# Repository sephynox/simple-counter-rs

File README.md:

# Simple 7-Segment Display Controller

A Rust-based PlatformIO Arduino project for controlling a 4-digit 7-segment
display with incrementing counter functionality. The purpose of this project is
to develop a simple PCB, software, and case design as a template for developing
hardware devices from ideation to production.

## Features

- Efficient multiplexed display using 74HC595 shift registers
- Safe interrupt handling with Mutex
- Hardware abstraction layer for Arduino integration

## Circuit Diagram

## Breadboard Design

## PCB Design

# PCB Assembled

## Case Design

## Hardware Setup

- Arduino Uno R3
- 2x 74HC595 shift registers
- 4-digit 7-segment display (common cathode)
- 2x Ceramic capacitors (100nF)
- 1x 5-pin header for Arduino pins

## Prerequisites

- PlatformIO Core (CLI) or PlatformIO IDE
  ```bash
  cargo install cargo-pio
  ```
- Rust toolchain with AVR target:
  ```bash
  rustup override set nightly
  rustup target add avr-unknown-gnu-atmega328
  ```
- AVR-GCC toolchain
  ```bash
  sudo apt-get install -y gcc-avr binutils-avr avr-libc
  ```

## Install Dependencies

```bash
sudo apt-get install -y python3-venv # If not already installed
cargo install cargo-pio
```

## Building and Flashing

1. Clone the repository:

   ```bash
   git clone https://github.com/sephynox/simple-counter-rs
   cd simple-counter-rs
   ```

2. Build the project:

   ```bash
   cargo pio build
   ```

3. Flash the firmware to your Arduino Uno:

   ```bash
   cargo pio exec -- run --target upload
   ```

## How to Create a New Project

```bash
cargo pio new --board uno your-project-name
```

## License

This project is licensed under the MIT License - see the [LICENSE](LICENSE) file for details.

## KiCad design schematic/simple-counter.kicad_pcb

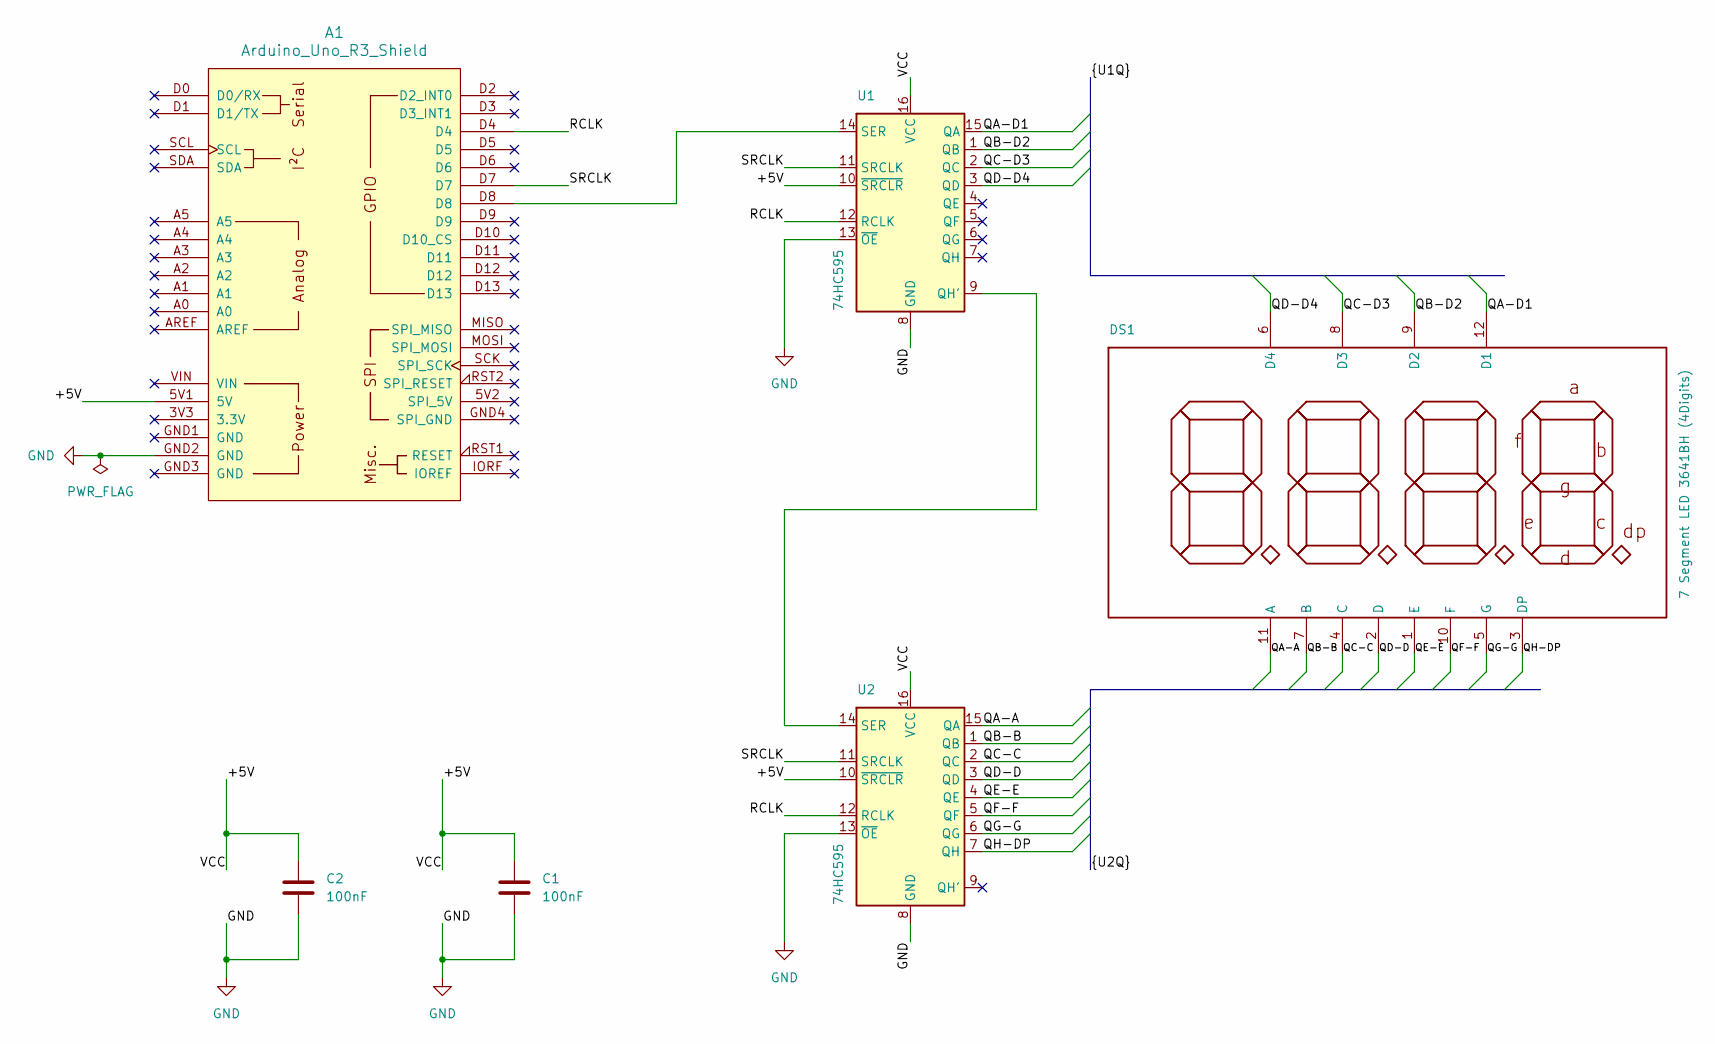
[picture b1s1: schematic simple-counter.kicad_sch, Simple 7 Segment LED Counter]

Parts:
A1: Arduino_Uno_R3_Shield; Arduino_Uno_R3_Shield_TW
C1, C2: 100nF; C_Disc_D5.0mm_W2.5mm_P2.50mm
DS1: 7 Segment LED 3641BH (4Digits); LEDSEG_0.36_4; Manufacturer Part 3641BH
U1, U2: 74HC595; DIP-16_W7.62mm_LongPads

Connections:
/+5V: A1.5V1 (5V), C1.1, C2.1, U1.10 (~SRCLR), U1.16 (VCC), U2.10 (~SRCLR), U2.16 (VCC)
/QA-A: DS1.11 (A), U2.15 (QA)
/QA-D1: DS1.12 (D1), U1.15 (QA)
/QB-B: DS1.7 (B), U2.1 (QB)
/QB-D2: DS1.9 (D2), U1.1 (QB)
/QC-C: DS1.4 (C), U2.2 (QC)
/QC-D3: DS1.8 (D3), U1.2 (QC)
/QD-D: DS1.2 (D), U2.3 (QD)
/QD-D4: DS1.6 (D4), U1.3 (QD)
/QE-E: DS1.1 (E), U2.4 (QE)
/QF-F: DS1.10 (F), U2.5 (QF)
/QG-G: DS1.5 (G), U2.6 (QG)
/QH-DP: DS1.3 (DP), U2.7 (QH)
/RCLK: A1.D4, U1.12 (RCLK), U2.12 (RCLK)
/SRCLK: A1.D7, U1.11 (SRCLK), U2.11 (SRCLK)
GND: A1.GND2 (GND), C1.2, C2.2, U1.8 (GND), U1.13 (~OE), U2.8 (GND), U2.13 (~OE)
unnamed: U1.9 (QH'), U2.14 (SER)
unnamed: A1.D8, U1.14 (SER)

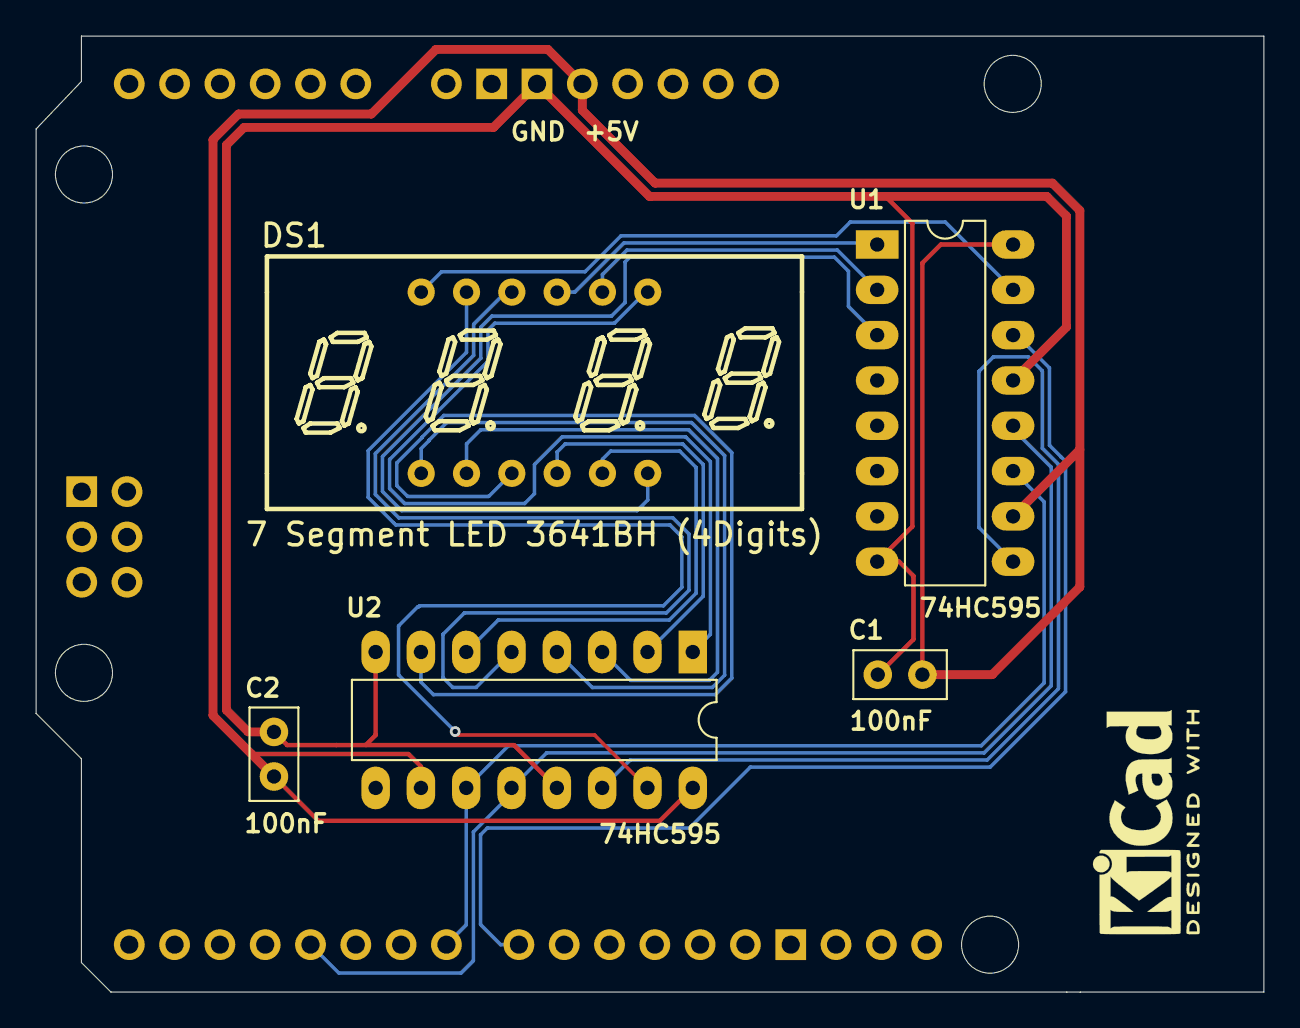
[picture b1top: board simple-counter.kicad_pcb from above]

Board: 2 copper layers, 68.8 x 53.6 mm, 8 parts (0 on the bottom side), 18 nets.

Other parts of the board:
Graphic_KiCad: KiCad-Logo2_5mm_SilkScreen
Graphic_QR: GitHub; simple-counter-rs-qr

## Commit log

2025-02-15 Initial commit.
2025-02-15 Cleanup doc images and silkscreen.
2025-02-16 Add gerber files and cleanup.
2025-02-17 Cleanup.
2025-03-07 Update configurations.
2025-03-07 Addlogging and tests.
2025-03-07 Add case designs.
2025-03-07 Update readme.
